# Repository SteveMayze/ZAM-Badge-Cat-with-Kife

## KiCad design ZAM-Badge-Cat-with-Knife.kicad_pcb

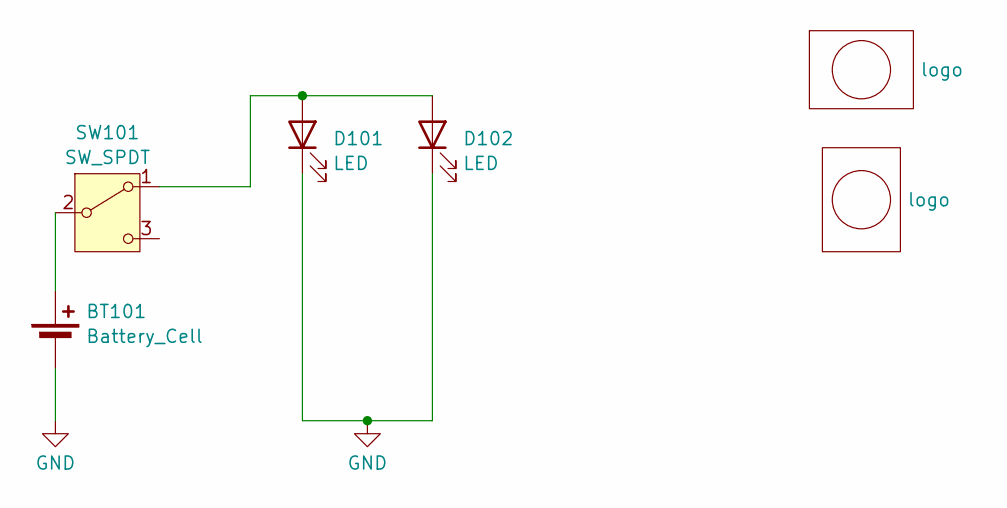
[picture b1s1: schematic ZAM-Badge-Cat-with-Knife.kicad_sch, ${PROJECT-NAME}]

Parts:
BT101: Battery_Cell; CR1220_Halter
D101, D102: LED; LED D5.0mm SMD
Lg101: logo; ZAM_LOGO_440
Lg102: logo; Butterfy-Pin
SW101: SW_SPDT; SW_SPDT_PCM12

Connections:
GND: BT101.2 (-), D101.1 (K), D102.1 (K)
unnamed: BT101.1 (+), SW101.2 (B)
unnamed: D101.2 (A), D102.2 (A), SW101.1 (A)

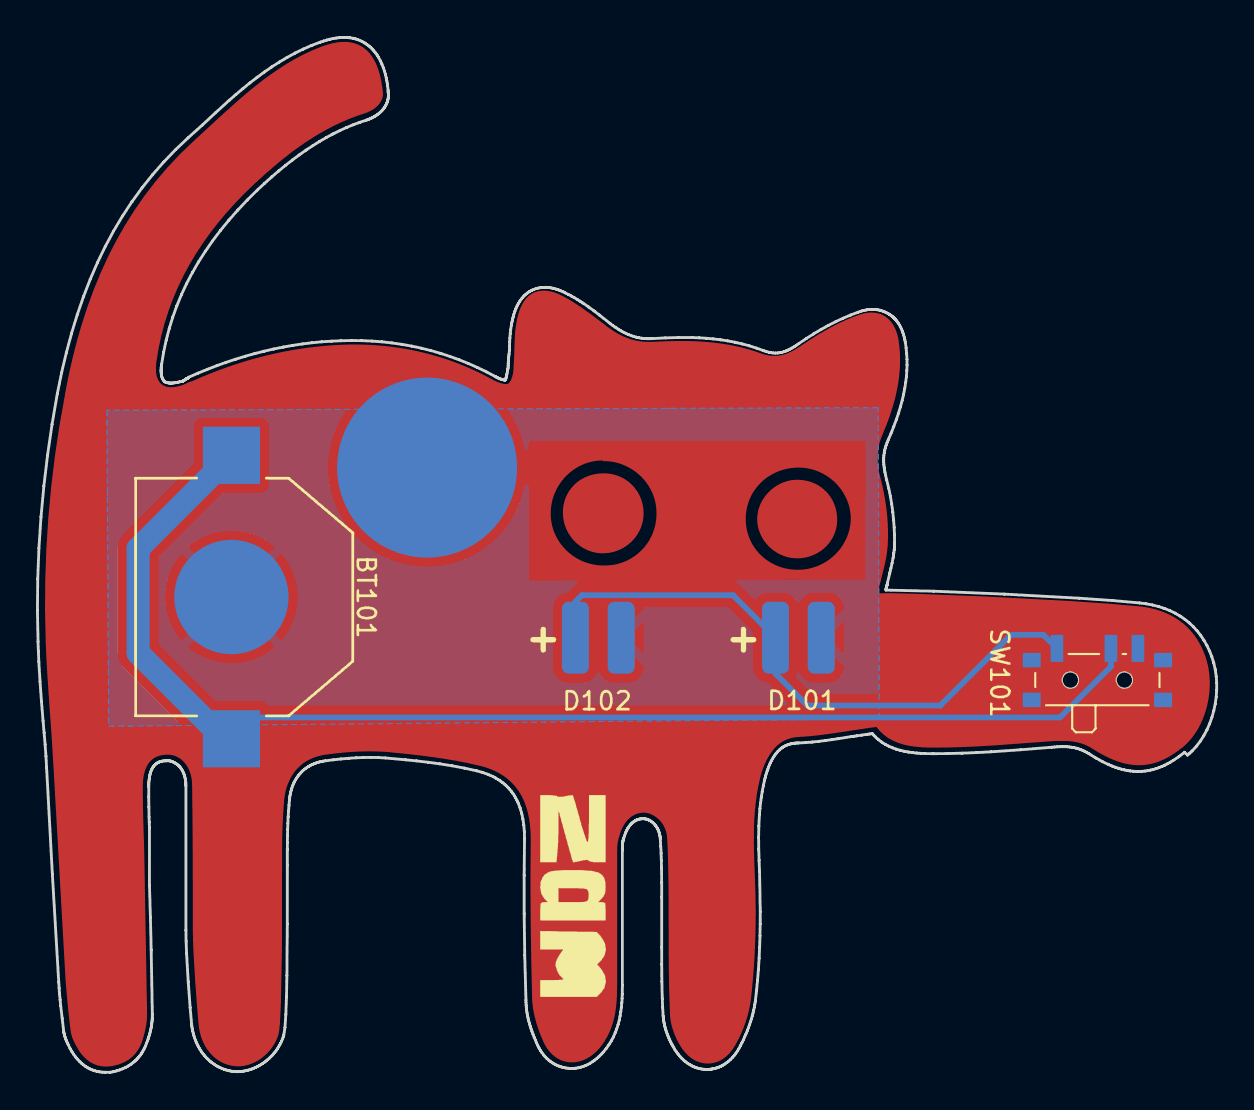
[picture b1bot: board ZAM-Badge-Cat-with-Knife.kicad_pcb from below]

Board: 2 copper layers, 65.5 x 57.5 mm, 6 parts (6 on the bottom side), 3 nets.

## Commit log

2025-02-11 Initial checkin
2025-02-11 Draft layout
2025-02-11 Finalise the layout and add ZAM logo and a placeholder for the butterfly pin
